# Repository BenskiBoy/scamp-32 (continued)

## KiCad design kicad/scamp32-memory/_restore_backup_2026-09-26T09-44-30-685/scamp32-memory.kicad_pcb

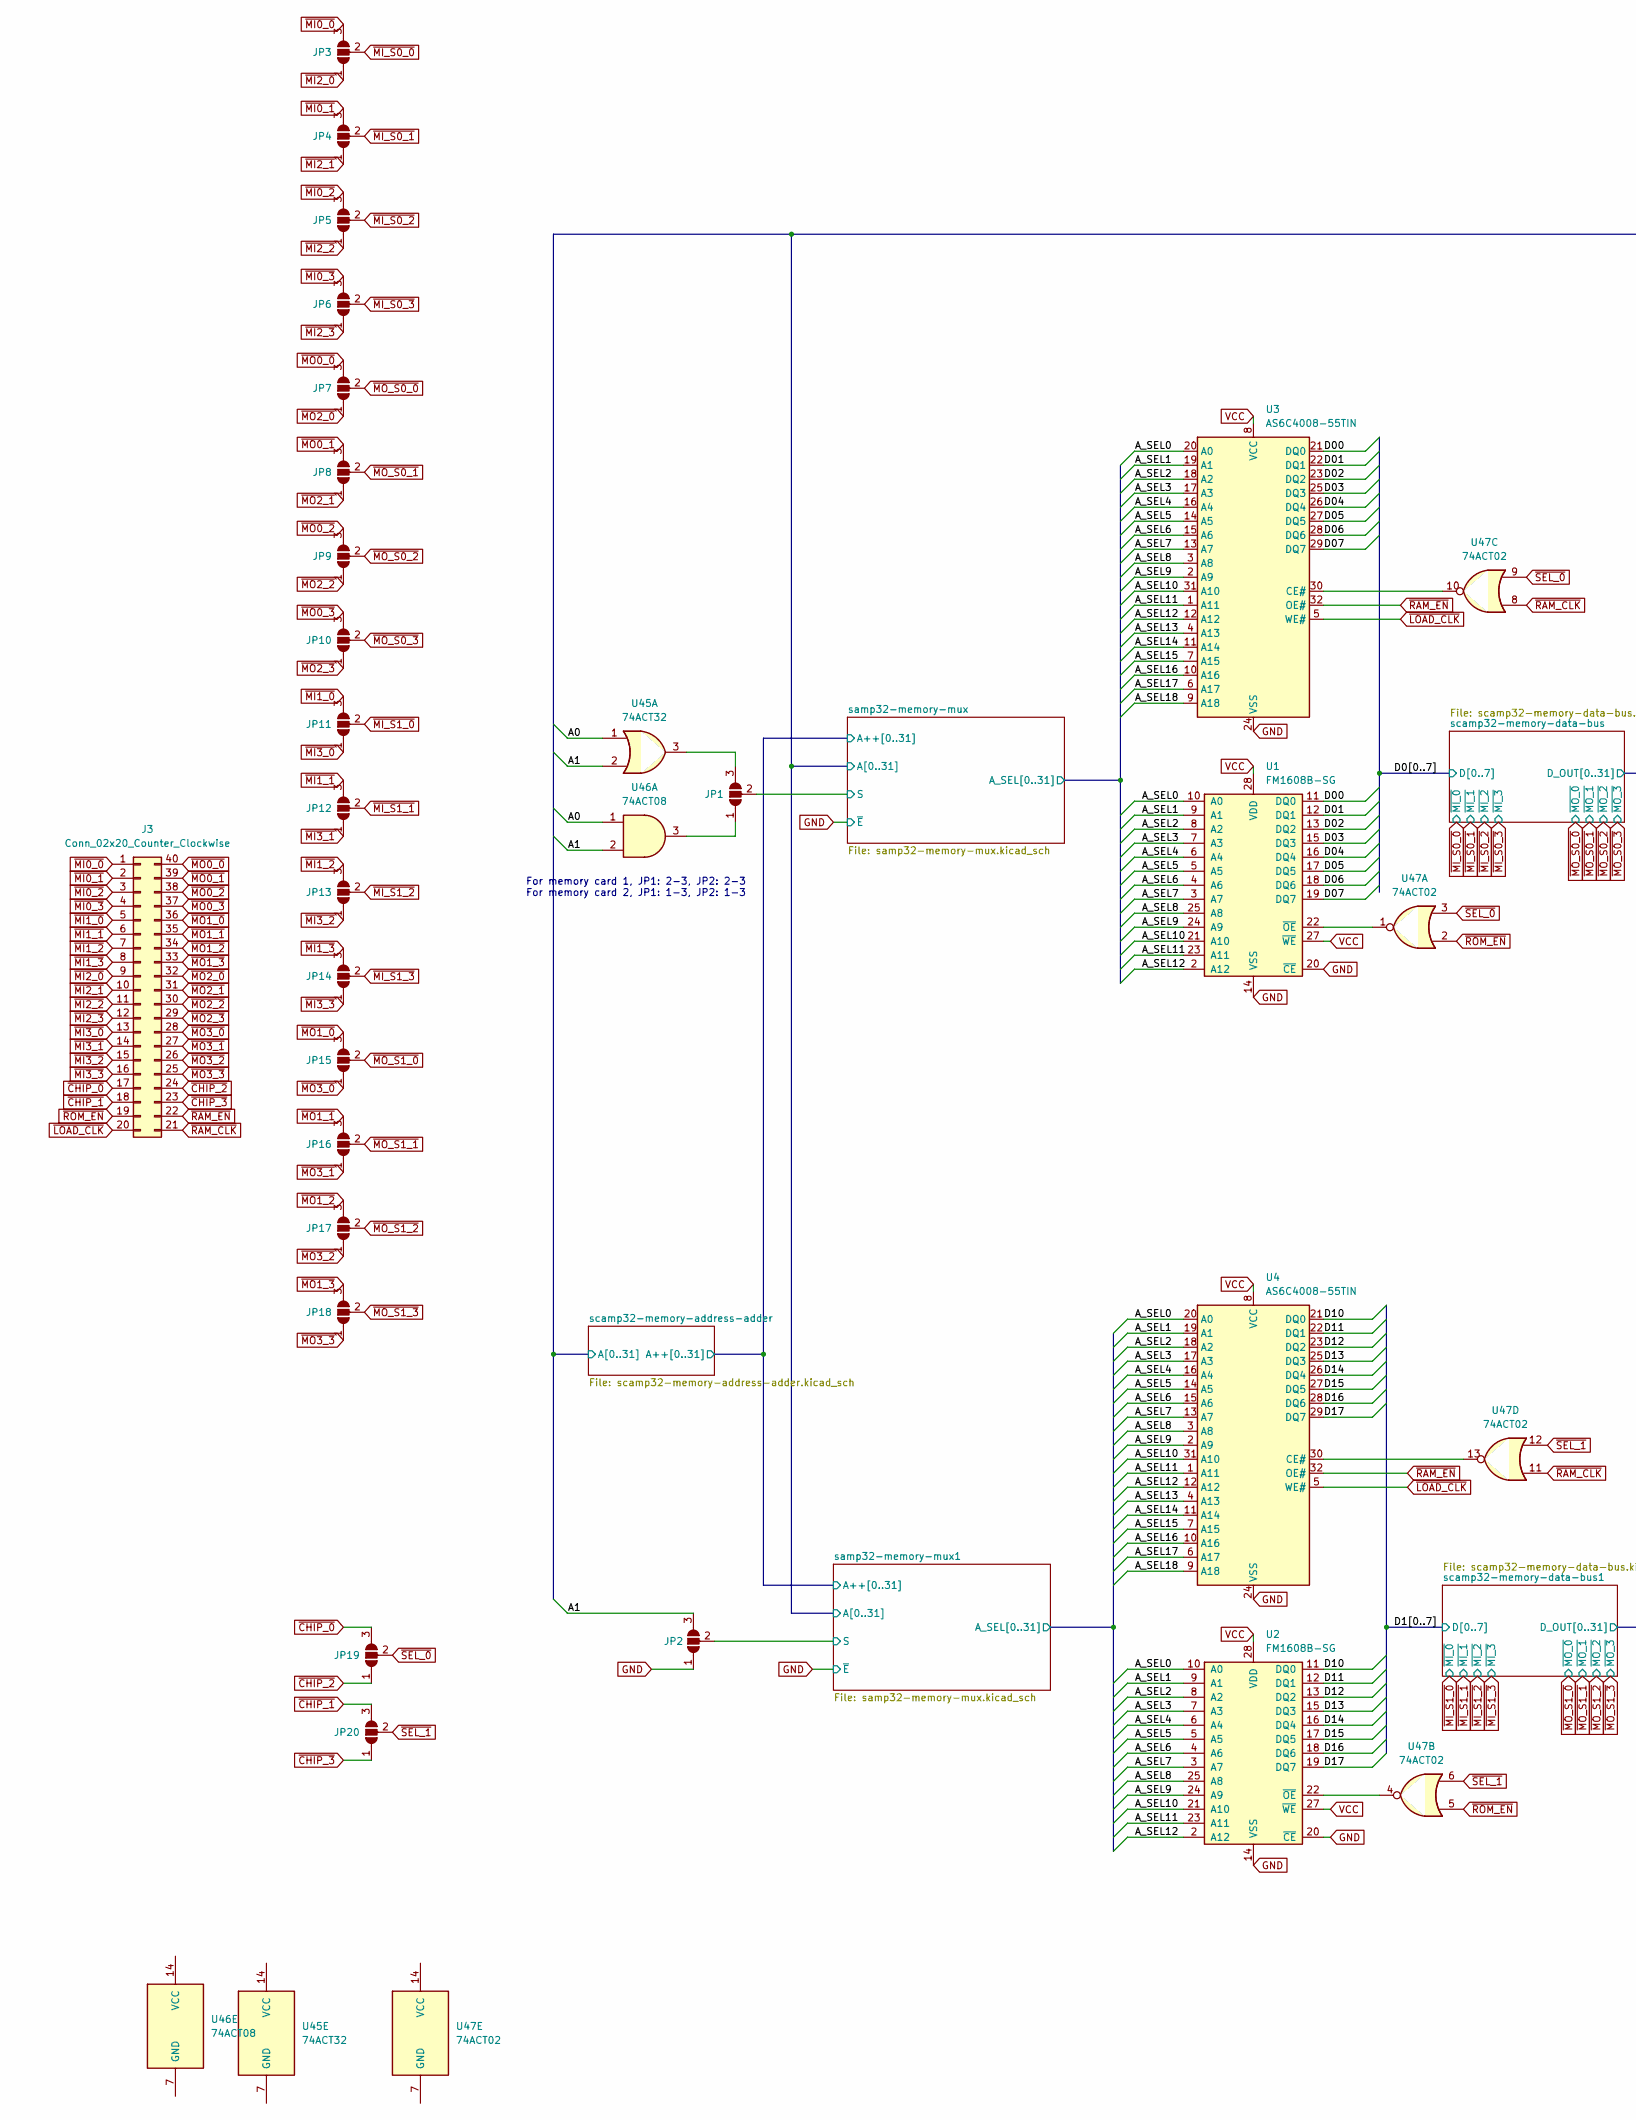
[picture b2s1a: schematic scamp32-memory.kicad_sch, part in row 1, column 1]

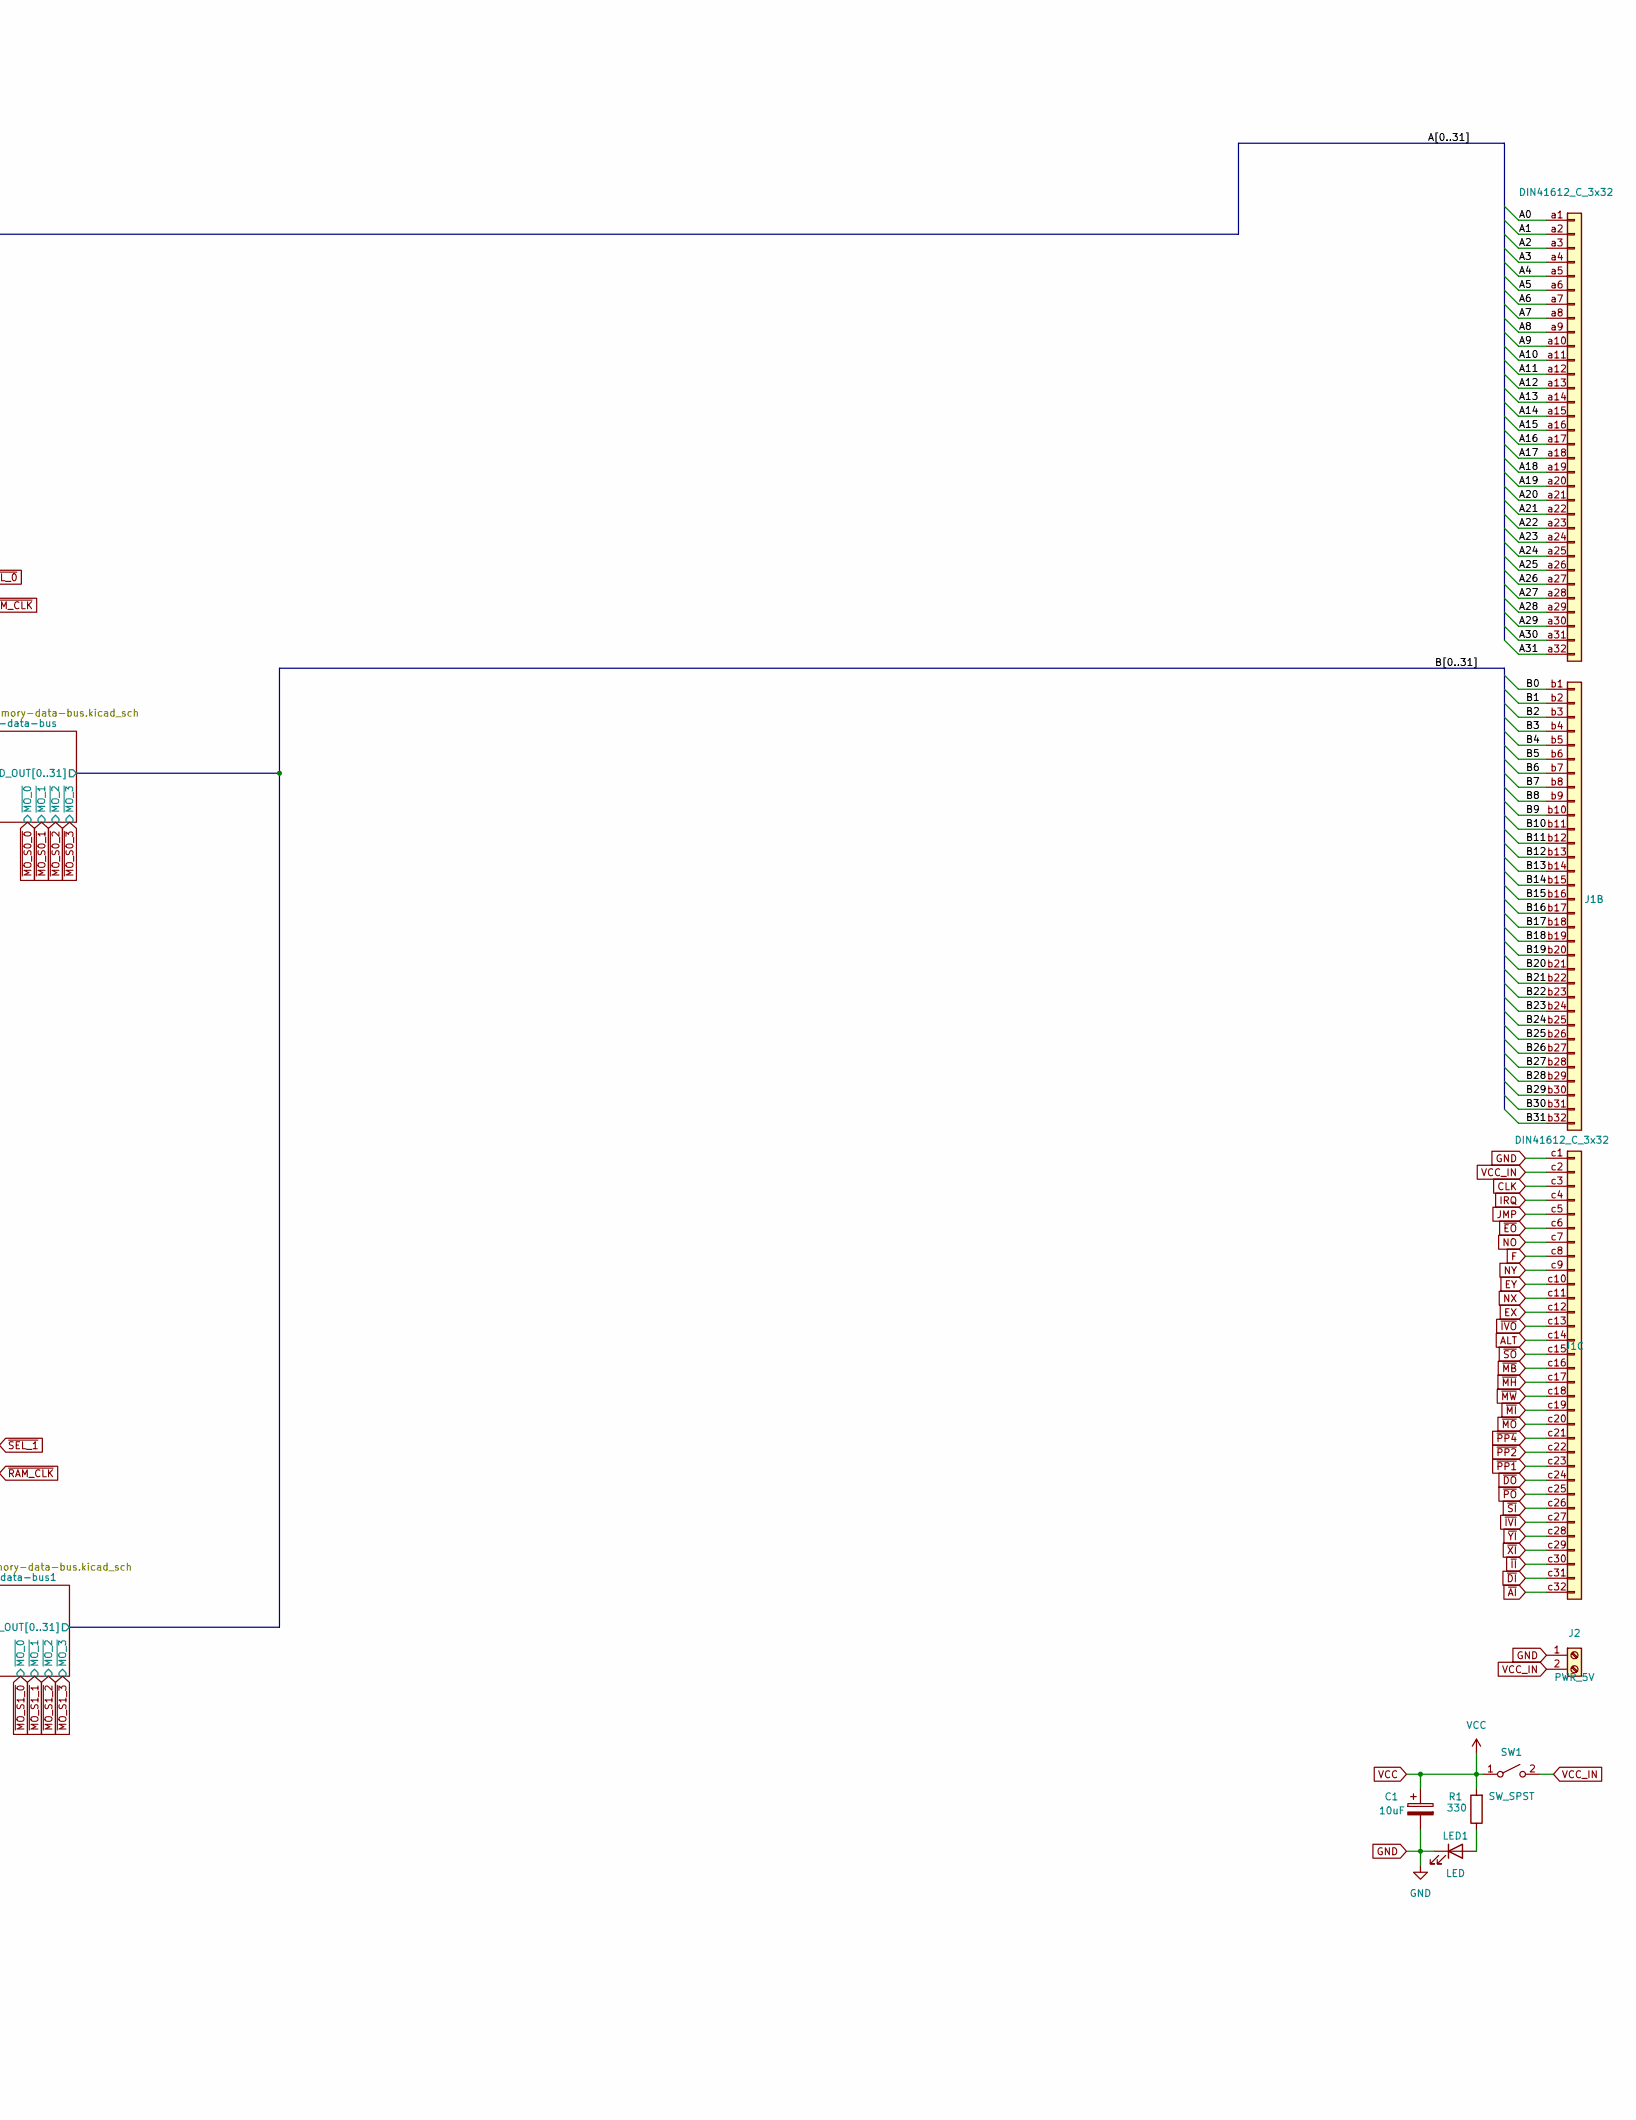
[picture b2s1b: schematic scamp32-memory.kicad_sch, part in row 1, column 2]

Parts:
C1: 10uF; CP_Radial_D5.0mm_P2.00mm
J1: DIN41612_C_3x32; DIN41612_C_3x32_Male_Horizontal_THT
J2: PWR_5V; TerminalBlock_Phoenix_MKDS-1,5-2-5.08_1x02_P5.08mm_Horizont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
J3: Conn_02x20_Counter_Clockwise; IDC-Header_2x20_P2.54mm_Horizontal
JP1, JP2, JP3, JP4, JP5, JP6, JP7, JP8, JP9, JP10, JP11, JP12, JP13, JP14, JP15, JP16, JP17, JP18, JP19, JP20: SolderJumper_3_Open; SolderJumper-3_P1.3mm_Open_RoundedPad1.0x1.5mm_NumberLabels
LED1: LED; LED_0805_2012Metric
R1: 330; R_0805_2012Metric
SW1: SW_SPST; SW_Slide_SPDT_Straight_CK_OS102011MS2Q
U1, U2: FM1608B-SG; DIP_Socket-28_W11.9mm_W12.7mm_W15.24mm_W17.78mm_W18.5mm_3M_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
U3, U4: AS6C4008-55TIN; TSOP-I-32_18.4x8mm_P0.5mm
U45: 74ACT32; SOIC-14_3.9x8.7mm_P1.27mm
U46: 74ACT08; TSSOP-14_4.4x5mm_P0.65mm
U47: 74ACT02; TSSOP-14_4.4x5mm_P0.65mm

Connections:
/A0: J1.a1, U45.1, U46.1; also elsewhere on the board
/A1: J1.a2, JP2.3 (B), U45.2, U46.2; also elsewhere on the board
/A2: J1.a3; also elsewhere on the board
/A3: J1.a4; also elsewhere on the board
/A4: J1.a5; also elsewhere on the board
/A5: J1.a6; also elsewhere on the board
/A6: J1.a7; also elsewhere on the board
/A7: J1.a8; also elsewhere on the board
/A8: J1.a9; also elsewhere on the board
/A9: J1.a10; also elsewhere on the board
/A10: J1.a11; also elsewhere on the board
/A11: J1.a12; also elsewhere on the board
/A12: J1.a13; also elsewhere on the board
/A13: J1.a14; also elsewhere on the board
/A14: J1.a15; also elsewhere on the board
/A15: J1.a16; also elsewhere on the board
/A16: J1.a17; also elsewhere on the board
/A17: J1.a18; also elsewhere on the board
/A18: J1.a19; also elsewhere on the board
/A19: J1.a20; also elsewhere on the board
/A20: J1.a21; also elsewhere on the board
/A21: J1.a22; also elsewhere on the board
/A22: J1.a23; also elsewhere on the board
/A23: J1.a24; also elsewhere on the board
/A24: J1.a25; also elsewhere on the board
/A25: J1.a26; also elsewhere on the board
/A26: J1.a27; also elsewhere on the board
/A27: J1.a28; also elsewhere on the board
/A28: J1.a29; also elsewhere on the board
/A29: J1.a30; also elsewhere on the board
/A30: J1.a31; also elsewhere on the board
/A31: J1.a32; also elsewhere on the board
/B0: J1.b1; also elsewhere on the board
/B1: J1.b2; also elsewhere on the board
/B2: J1.b3; also elsewhere on the board
/B3: J1.b4; also elsewhere on the board
/B4: J1.b5; also elsewhere on the board
/B5: J1.b6; also elsewhere on the board
/B6: J1.b7; also elsewhere on the board
/B7: J1.b8; also elsewhere on the board
/B8: J1.b9; also elsewhere on the board
/B9: J1.b10; also elsewhere on the board
/B10: J1.b11; also elsewhere on the board
/B11: J1.b12; also elsewhere on the board
/B12: J1.b13; also elsewhere on the board
/B13: J1.b14; also elsewhere on the board
/B14: J1.b15; also elsewhere on the board
/B15: J1.b16; also elsewhere on the board
/B16: J1.b17; also elsewhere on the board
/B17: J1.b18; also elsewhere on the board
/B18: J1.b19; also elsewhere on the board
/B19: J1.b20; also elsewhere on the board
/B20: J1.b21; also elsewhere on the board
/B21: J1.b22; also elsewhere on the board
/B22: J1.b23; also elsewhere on the board
/B23: J1.b24; also elsewhere on the board
/B24: J1.b25; also elsewhere on the board
/B25: J1.b26; also elsewhere on the board
/B26: J1.b27; also elsewhere on the board
/B27: J1.b28; also elsewhere on the board
/B28: J1.b29; also elsewhere on the board
/B29: J1.b30; also elsewhere on the board
/B30: J1.b31; also elsewhere on the board
/B31: J1.b32; also elsewhere on the board
/D00: U1.11 (DQ0), U3.21 (DQ0); also elsewhere on the board
/D01: U1.12 (DQ1), U3.22 (DQ1); also elsewhere on the board
/D02: U1.13 (DQ2), U3.23 (DQ2); also elsewhere on the board
/D03: U1.15 (DQ3), U3.25 (DQ3); also elsewhere on the board
/D04: U1.16 (DQ4), U3.26 (DQ4); also elsewhere on the board
/D05: U1.17 (DQ5), U3.27 (DQ5); also elsewhere on the board
/D06: U1.18 (DQ6), U3.28 (DQ6); also elsewhere on the board
/D07: U1.19 (DQ7), U3.29 (DQ7); also elsewhere on the board
/D10: U2.11 (DQ0), U4.21 (DQ0); also elsewhere on the board
/D11: U2.12 (DQ1), U4.22 (DQ1); also elsewhere on the board
/D12: U2.13 (DQ2), U4.23 (DQ2); also elsewhere on the board
/D13: U2.15 (DQ3), U4.25 (DQ3); also elsewhere on the board
/D14: U2.16 (DQ4), U4.26 (DQ4); also elsewhere on the board
/D15: U2.17 (DQ5), U4.27 (DQ5); also elsewhere on the board
/D16: U2.18 (DQ6), U4.28 (DQ6); also elsewhere on the board
/D17: U2.19 (DQ7), U4.29 (DQ7); also elsewhere on the board
/samp32-memory-mux1/S: JP2.2 (C); also elsewhere on the board
/samp32-memory-mux/A_SEL0: U1.10 (A0), U2.10 (A0), U3.20 (A0), U4.20 (A0); also elsewhere on the board
/samp32-memory-mux/A_SEL1: U1.9 (A1), U2.9 (A1), U3.19 (A1), U4.19 (A1); also elsewhere on the board
/samp32-memory-mux/A_SEL2: U1.8 (A2), U2.8 (A2), U3.18 (A2), U4.18 (A2); also elsewhere on the board
/samp32-memory-mux/A_SEL3: U1.7 (A3), U2.7 (A3), U3.17 (A3), U4.17 (A3); also elsewhere on the board
/samp32-memory-mux/A_SEL4: U1.6 (A4), U2.6 (A4), U3.16 (A4), U4.16 (A4); also elsewhere on the board
/samp32-memory-mux/A_SEL5: U1.5 (A5), U2.5 (A5), U3.14 (A5), U4.14 (A5); also elsewhere on the board
/samp32-memory-mux/A_SEL6: U1.4 (A6), U2.4 (A6), U3.15 (A6), U4.15 (A6); also elsewhere on the board
/samp32-memory-mux/A_SEL7: U1.3 (A7), U2.3 (A7), U3.13 (A7), U4.13 (A7); also elsewhere on the board
/samp32-memory-mux/A_SEL8: U1.25 (A8), U2.25 (A8), U3.3 (A8), U4.3 (A8); also elsewhere on the board
/samp32-memory-mux/A_SEL9: U1.24 (A9), U2.24 (A9), U3.2 (A9), U4.2 (A9); also elsewhere on the board
/samp32-memory-mux/A_SEL10: U1.21 (A10), U2.21 (A10), U3.31 (A10), U4.31 (A10); also elsewhere on the board
/samp32-memory-mux/A_SEL11: U1.23 (A11), U2.23 (A11), U3.1 (A11), U4.1 (A11); also elsewhere on the board
/samp32-memory-mux/A_SEL12: U1.2 (A12), U2.2 (A12), U3.12 (A12), U4.12 (A12); also elsewhere on the board
/samp32-memory-mux/A_SEL13: U3.4 (A13), U4.4 (A13); also elsewhere on the board
/samp32-memory-mux/A_SEL14: U3.11 (A14), U4.11 (A14); also elsewhere on the board
/samp32-memory-mux/A_SEL15: U3.7 (A15), U4.7 (A15); also elsewhere on the board
/samp32-memory-mux/A_SEL16: U3.10 (A16), U4.10 (A16); also elsewhere on the board
/samp32-memory-mux/A_SEL17: U3.6 (A17), U4.6 (A17); also elsewhere on the board
/samp32-memory-mux/A_SEL18: U3.9 (A18), U4.9 (A18); also elsewhere on the board
/samp32-memory-mux/S: JP1.2 (C); also elsewhere on the board
ALT: J1.c14
CLK: J1.c3
EX: J1.c12
EY: J1.c10
F: J1.c8
GND: C1.2, J1.c1, J2.1, JP2.1 (A), LED1.1 (K), U1.14 (VSS), U1.20 (~CE), U2.14 (VSS), U2.20 (~CE), U3.24 (VSS), U4.24 (VSS); also elsewhere on the board
IRQ: J1.c4
JMP: J1.c5
NO: J1.c7
NX: J1.c11
NY: J1.c9
unnamed: JP1.1 (A), U46.3
unnamed: JP1.3 (B), U45.3
unnamed: LED1.2 (A), R1.1
unnamed: U1.22 (~OE), U47.1
unnamed: U2.22 (~OE), U47.4
unnamed: U3.30 (CE#), U47.10
unnamed: U4.30 (CE#), U47.13
VCC: C1.1, R1.2, SW1.1 (A), U1.27 (~WE), U1.28 (VDD), U2.27 (~WE), U2.28 (VDD), U3.8 (VCC), U4.8 (VCC); also elsewhere on the board
VCC_IN: J1.c2, J2.2, SW1.2 (B)
~AI: J1.c32
~CHIP_0: J3.17, JP19.3 (B)
~CHIP_1: J3.18, JP20.3 (B)
~CHIP_2: J3.24, JP19.1 (A)
~CHIP_3: J3.23, JP20.1 (A)
~DI: J1.c31
~DO: J1.c24
~EO: J1.c6
~II: J1.c30
~IVI: J1.c27
~IVO: J1.c13
~LOAD_CLK: J3.20, U3.5 (WE#), U4.5 (WE#)
~MB: J1.c16
~MH: J1.c17
~MI0_0: J3.1, JP3.3 (B)
~MI0_1: J3.2, JP4.3 (B)
~MI0_2: J3.3, JP5.3 (B)
~MI0_3: J3.4, JP6.3 (B)
~MI1_0: J3.5, JP11.3 (B)
~MI1_1: J3.6, JP12.3 (B)
~MI1_2: J3.7, JP13.3 (B)
~MI1_3: J3.8, JP14.3 (B)
~MI2_0: J3.9, JP3.1 (A)
~MI2_1: J3.10, JP4.1 (A)
~MI2_2: J3.11, JP5.1 (A)
~MI2_3: J3.12, JP6.1 (A)
~MI3_0: J3.13, JP11.1 (A)
~MI3_1: J3.14, JP12.1 (A)
~MI3_2: J3.15, JP13.1 (A)
~MI3_3: J3.16, JP14.1 (A)
~MI_S0_0: JP3.2 (C); also elsewhere on the board
~MI_S0_1: JP4.2 (C); also elsewhere on the board
~MI_S0_2: JP5.2 (C); also elsewhere on the board
~MI_S0_3: JP6.2 (C); also elsewhere on the board
~MI_S1_0: JP11.2 (C); also elsewhere on the board
~MI_S1_1: JP12.2 (C); also elsewhere on the board
~MI_S1_2: JP13.2 (C); also elsewhere on the board
~MI_S1_3: JP14.2 (C); also elsewhere on the board
~MI: J1.c19
~MO0_0: J3.40, JP7.3 (B)
~MO0_1: J3.39, JP8.3 (B)
~MO0_2: J3.38, JP9.3 (B)
~MO0_3: J3.37, JP10.3 (B)
~MO1_0: J3.36, JP15.3 (B)
~MO1_1: J3.35, JP16.3 (B)
~MO1_2: J3.34, JP17.3 (B)
~MO1_3: J3.33, JP18.3 (B)
~MO2_0: J3.32, JP7.1 (A)
~MO2_1: J3.31, JP8.1 (A)
~MO2_2: J3.30, JP9.1 (A)
~MO2_3: J3.29, JP10.1 (A)
~MO3_0: J3.28, JP15.1 (A)
~MO3_1: J3.27, JP16.1 (A)
~MO3_2: J3.26, JP17.1 (A)
~MO3_3: J3.25, JP18.1 (A)
~MO_S0_0: JP7.2 (C); also elsewhere on the board
~MO_S0_1: JP8.2 (C); also elsewhere on the board
~MO_S0_2: JP9.2 (C); also elsewhere on the board
~MO_S0_3: JP10.2 (C); also elsewhere on the board
~MO_S1_0: JP15.2 (C); also elsewhere on the board
~MO_S1_1: JP16.2 (C); also elsewhere on the board
~MO_S1_2: JP17.2 (C); also elsewhere on the board
~MO_S1_3: JP18.2 (C); also elsewhere on the board
~MO: J1.c20
~MW: J1.c18
~PO: J1.c25
~PP1: J1.c23
~PP2: J1.c22
~PP4: J1.c21
~RAM_CLK: J3.21, U47.8, U47.11
~RAM_EN: J3.22, U3.32 (OE#), U4.32 (OE#)
~ROM_EN: J3.19, U47.2, U47.5
~SEL_0: JP19.2 (C), U47.3, U47.9
~SEL_1: JP20.2 (C), U47.6, U47.12
~SI: J1.c26
~SO: J1.c15
~XI: J1.c29
~YI: J1.c28

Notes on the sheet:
For memory card 1, JP1: 2-3, JP2: 2-3 For memory card 2, JP1: 1-3, JP2: 1-3

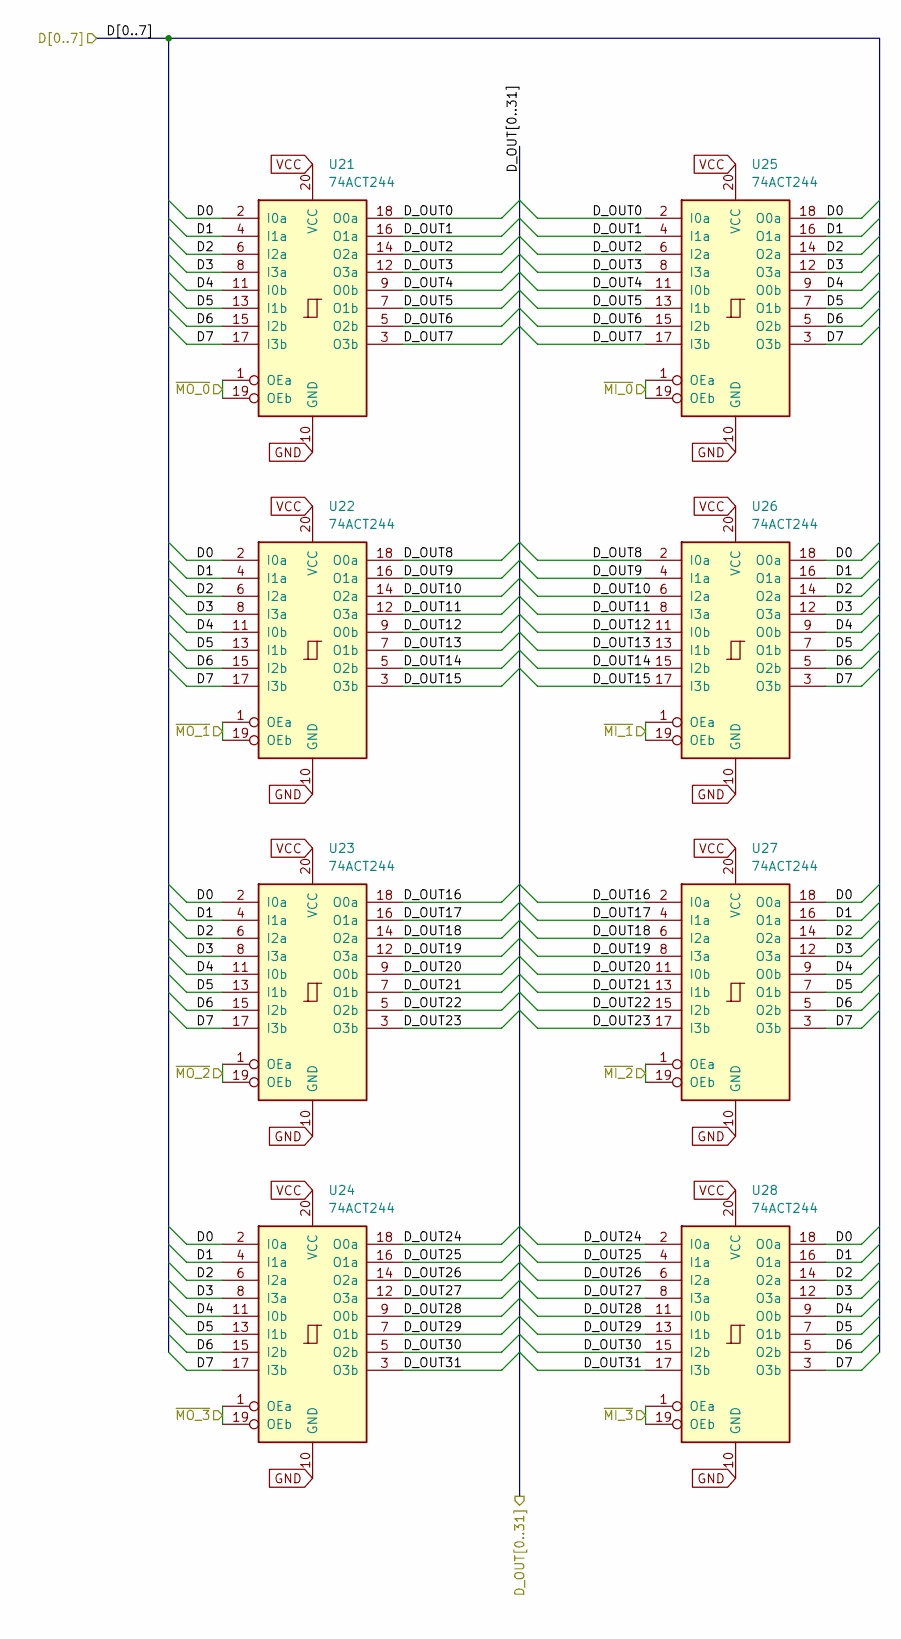
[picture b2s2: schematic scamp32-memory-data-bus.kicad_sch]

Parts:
U21, U22, U23, U24, U25, U26, U27, U28: 74ACT244; Texas_PW0020A_TSSOP-20_4.4x6.5mm_P0.65mm

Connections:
/B0: U21.18 (O0a), U25.2 (I0a); also elsewhere on the board
/B1: U21.16 (O1a), U25.4 (I1a); also elsewhere on the board
/B2: U21.14 (O2a), U25.6 (I2a); also elsewhere on the board
/B3: U21.12 (O3a), U25.8 (I3a); also elsewhere on the board
/B4: U21.9 (O0b), U25.11 (I0b); also elsewhere on the board
/B5: U21.7 (O1b), U25.13 (I1b); also elsewhere on the board
/B6: U21.5 (O2b), U25.15 (I2b); also elsewhere on the board
/B7: U21.3 (O3b), U25.17 (I3b); also elsewhere on the board
/B8: U22.18 (O0a), U26.2 (I0a); also elsewhere on the board
/B9: U22.16 (O1a), U26.4 (I1a); also elsewhere on the board
/B10: U22.14 (O2a), U26.6 (I2a); also elsewhere on the board
/B11: U22.12 (O3a), U26.8 (I3a); also elsewhere on the board
/B12: U22.9 (O0b), U26.11 (I0b); also elsewhere on the board
/B13: U22.7 (O1b), U26.13 (I1b); also elsewhere on the board
/B14: U22.5 (O2b), U26.15 (I2b); also elsewhere on the board
/B15: U22.3 (O3b), U26.17 (I3b); also elsewhere on the board
/B16: U23.18 (O0a), U27.2 (I0a); also elsewhere on the board
/B17: U23.16 (O1a), U27.4 (I1a); also elsewhere on the board
/B18: U23.14 (O2a), U27.6 (I2a); also elsewhere on the board
/B19: U23.12 (O3a), U27.8 (I3a); also elsewhere on the board
/B20: U23.9 (O0b), U27.11 (I0b); also elsewhere on the board
/B21: U23.7 (O1b), U27.13 (I1b); also elsewhere on the board
/B22: U23.5 (O2b), U27.15 (I2b); also elsewhere on the board
/B23: U23.3 (O3b), U27.17 (I3b); also elsewhere on the board
/B24: U24.18 (O0a), U28.2 (I0a); also elsewhere on the board
/B25: U24.16 (O1a), U28.4 (I1a); also elsewhere on the board
/B26: U24.14 (O2a), U28.6 (I2a); also elsewhere on the board
/B27: U24.12 (O3a), U28.8 (I3a); also elsewhere on the board
/B28: U24.9 (O0b), U28.11 (I0b); also elsewhere on the board
/B29: U24.7 (O1b), U28.13 (I1b); also elsewhere on the board
/B30: U24.5 (O2b), U28.15 (I2b); also elsewhere on the board
/B31: U24.3 (O3b), U28.17 (I3b); also elsewhere on the board
/D00: U21.2 (I0a), U22.2 (I0a), U23.2 (I0a), U24.2 (I0a), U25.18 (O0a), U26.18 (O0a), U27.18 (O0a), U28.18 (O0a); also elsewhere on the board
/D01: U21.4 (I1a), U22.4 (I1a), U23.4 (I1a), U24.4 (I1a), U25.16 (O1a), U26.16 (O1a), U27.16 (O1a), U28.16 (O1a); also elsewhere on the board
/D02: U21.6 (I2a), U22.6 (I2a), U23.6 (I2a), U24.6 (I2a), U25.14 (O2a), U26.14 (O2a), U27.14 (O2a), U28.14 (O2a); also elsewhere on the board
/D03: U21.8 (I3a), U22.8 (I3a), U23.8 (I3a), U24.8 (I3a), U25.12 (O3a), U26.12 (O3a), U27.12 (O3a), U28.12 (O3a); also elsewhere on the board
/D04: U21.11 (I0b), U22.11 (I0b), U23.11 (I0b), U24.11 (I0b), U25.9 (O0b), U26.9 (O0b), U27.9 (O0b), U28.9 (O0b); also elsewhere on the board
/D05: U21.13 (I1b), U22.13 (I1b), U23.13 (I1b), U24.13 (I1b), U25.7 (O1b), U26.7 (O1b), U27.7 (O1b), U28.7 (O1b); also elsewhere on the board
/D06: U21.15 (I2b), U22.15 (I2b), U23.15 (I2b), U24.15 (I2b), U25.5 (O2b), U26.5 (O2b), U27.5 (O2b), U28.5 (O2b); also elsewhere on the board
/D07: U21.17 (I3b), U22.17 (I3b), U23.17 (I3b), U24.17 (I3b), U25.3 (O3b), U26.3 (O3b), U27.3 (O3b), U28.3 (O3b); also elsewhere on the board
GND: U21.10 (GND), U22.10 (GND), U23.10 (GND), U24.10 (GND), U25.10 (GND), U26.10 (GND), U27.10 (GND), U28.10 (GND); also elsewhere on the board
VCC: U21.20 (VCC), U22.20 (VCC), U23.20 (VCC), U24.20 (VCC), U25.20 (VCC), U26.20 (VCC), U27.20 (VCC), U28.20 (VCC); also elsewhere on the board
~MI_S0_0: U25.1 (OEa), U25.19 (OEb); also elsewhere on the board
~MI_S0_1: U26.1 (OEa), U26.19 (OEb); also elsewhere on the board
~MI_S0_2: U27.1 (OEa), U27.19 (OEb); also elsewhere on the board
~MI_S0_3: U28.1 (OEa), U28.19 (OEb); also elsewhere on the board
~MO_S0_0: U21.1 (OEa), U21.19 (OEb); also elsewhere on the board
~MO_S0_1: U22.1 (OEa), U22.19 (OEb); also elsewhere on the board
~MO_S0_2: U23.1 (OEa), U23.19 (OEb); also elsewhere on the board
~MO_S0_3: U24.1 (OEa), U24.19 (OEb); also elsewhere on the board

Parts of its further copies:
U29, U30, U31, U32, U33, U34, U35, U36: 74ACT244; Texas_PW0020A_TSSOP-20_4.4x6.5mm_P0.65mm

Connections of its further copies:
/B0: U29.18 (O0a), U33.2 (I0a); also elsewhere on the board
/B1: U29.16 (O1a), U33.4 (I1a); also elsewhere on the board
/B2: U29.14 (O2a), U33.6 (I2a); also elsewhere on the board
/B3: U29.12 (O3a), U33.8 (I3a); also elsewhere on the board
/B4: U29.9 (O0b), U33.11 (I0b); also elsewhere on the board
/B5: U29.7 (O1b), U33.13 (I1b); also elsewhere on the board
/B6: U29.5 (O2b), U33.15 (I2b); also elsewhere on the board
/B7: U29.3 (O3b), U33.17 (I3b); also elsewhere on the board
/B8: U30.18 (O0a), U34.2 (I0a); also elsewhere on the board
/B9: U30.16 (O1a), U34.4 (I1a); also elsewhere on the board
/B10: U30.14 (O2a), U34.6 (I2a); also elsewhere on the board
/B11: U30.12 (O3a), U34.8 (I3a); also elsewhere on the board
/B12: U30.9 (O0b), U34.11 (I0b); also elsewhere on the board
/B13: U30.7 (O1b), U34.13 (I1b); also elsewhere on the board
/B14: U30.5 (O2b), U34.15 (I2b); also elsewhere on the board
/B15: U30.3 (O3b), U34.17 (I3b); also elsewhere on the board
/B16: U31.18 (O0a), U35.2 (I0a); also elsewhere on the board
/B17: U31.16 (O1a), U35.4 (I1a); also elsewhere on the board
/B18: U31.14 (O2a), U35.6 (I2a); also elsewhere on the board
/B19: U31.12 (O3a), U35.8 (I3a); also elsewhere on the board
/B20: U31.9 (O0b), U35.11 (I0b); also elsewhere on the board
/B21: U31.7 (O1b), U35.13 (I1b); also elsewhere on the board
/B22: U31.5 (O2b), U35.15 (I2b); also elsewhere on the board
/B23: U31.3 (O3b), U35.17 (I3b); also elsewhere on the board
/B24: U32.18 (O0a), U36.2 (I0a); also elsewhere on the board
/B25: U32.16 (O1a), U36.4 (I1a); also elsewhere on the board
/B26: U32.14 (O2a), U36.6 (I2a); also elsewhere on the board
/B27: U32.12 (O3a), U36.8 (I3a); also elsewhere on the board
/B28: U32.9 (O0b), U36.11 (I0b); also elsewhere on the board
/B29: U32.7 (O1b), U36.13 (I1b); also elsewhere on the board
/B30: U32.5 (O2b), U36.15 (I2b); also elsewhere on the board
/B31: U32.3 (O3b), U36.17 (I3b); also elsewhere on the board
/D10: U29.2 (I0a), U30.2 (I0a), U31.2 (I0a), U32.2 (I0a), U33.18 (O0a), U34.18 (O0a), U35.18 (O0a), U36.18 (O0a); also elsewhere on the board
/D11: U29.4 (I1a), U30.4 (I1a), U31.4 (I1a), U32.4 (I1a), U33.16 (O1a), U34.16 (O1a), U35.16 (O1a), U36.16 (O1a); also elsewhere on the board
/D12: U29.6 (I2a), U30.6 (I2a), U31.6 (I2a), U32.6 (I2a), U33.14 (O2a), U34.14 (O2a), U35.14 (O2a), U36.14 (O2a); also elsewhere on the board
/D13: U29.8 (I3a), U30.8 (I3a), U31.8 (I3a), U32.8 (I3a), U33.12 (O3a), U34.12 (O3a), U35.12 (O3a), U36.12 (O3a); also elsewhere on the board
/D14: U29.11 (I0b), U30.11 (I0b), U31.11 (I0b), U32.11 (I0b), U33.9 (O0b), U34.9 (O0b), U35.9 (O0b), U36.9 (O0b); also elsewhere on the board
/D15: U29.13 (I1b), U30.13 (I1b), U31.13 (I1b), U32.13 (I1b), U33.7 (O1b), U34.7 (O1b), U35.7 (O1b), U36.7 (O1b); also elsewhere on the board
/D16: U29.15 (I2b), U30.15 (I2b), U31.15 (I2b), U32.15 (I2b), U33.5 (O2b), U34.5 (O2b), U35.5 (O2b), U36.5 (O2b); also elsewhere on the board
/D17: U29.17 (I3b), U30.17 (I3b), U31.17 (I3b), U32.17 (I3b), U33.3 (O3b), U34.3 (O3b), U35.3 (O3b), U36.3 (O3b); also elsewhere on the board
GND: U29.10 (GND), U30.10 (GND), U31.10 (GND), U32.10 (GND), U33.10 (GND), U34.10 (GND), U35.10 (GND), U36.10 (GND); also elsewhere on the board
VCC: U29.20 (VCC), U30.20 (VCC), U31.20 (VCC), U32.20 (VCC), U33.20 (VCC), U34.20 (VCC), U35.20 (VCC), U36.20 (VCC); also elsewhere on the board
~MI_S1_0: U33.1 (OEa), U33.19 (OEb); also elsewhere on the board
~MI_S1_1: U34.1 (OEa), U34.19 (OEb); also elsewhere on the board
~MI_S1_2: U35.1 (OEa), U35.19 (OEb); also elsewhere on the board
~MI_S1_3: U36.1 (OEa), U36.19 (OEb); also elsewhere on the board
~MO_S1_0: U29.1 (OEa), U29.19 (OEb); also elsewhere on the board
~MO_S1_1: U30.1 (OEa), U30.19 (OEb); also elsewhere on the board
~MO_S1_2: U31.1 (OEa), U31.19 (OEb); also elsewhere on the board
~MO_S1_3: U32.1 (OEa), U32.19 (OEb); also elsewhere on the board
